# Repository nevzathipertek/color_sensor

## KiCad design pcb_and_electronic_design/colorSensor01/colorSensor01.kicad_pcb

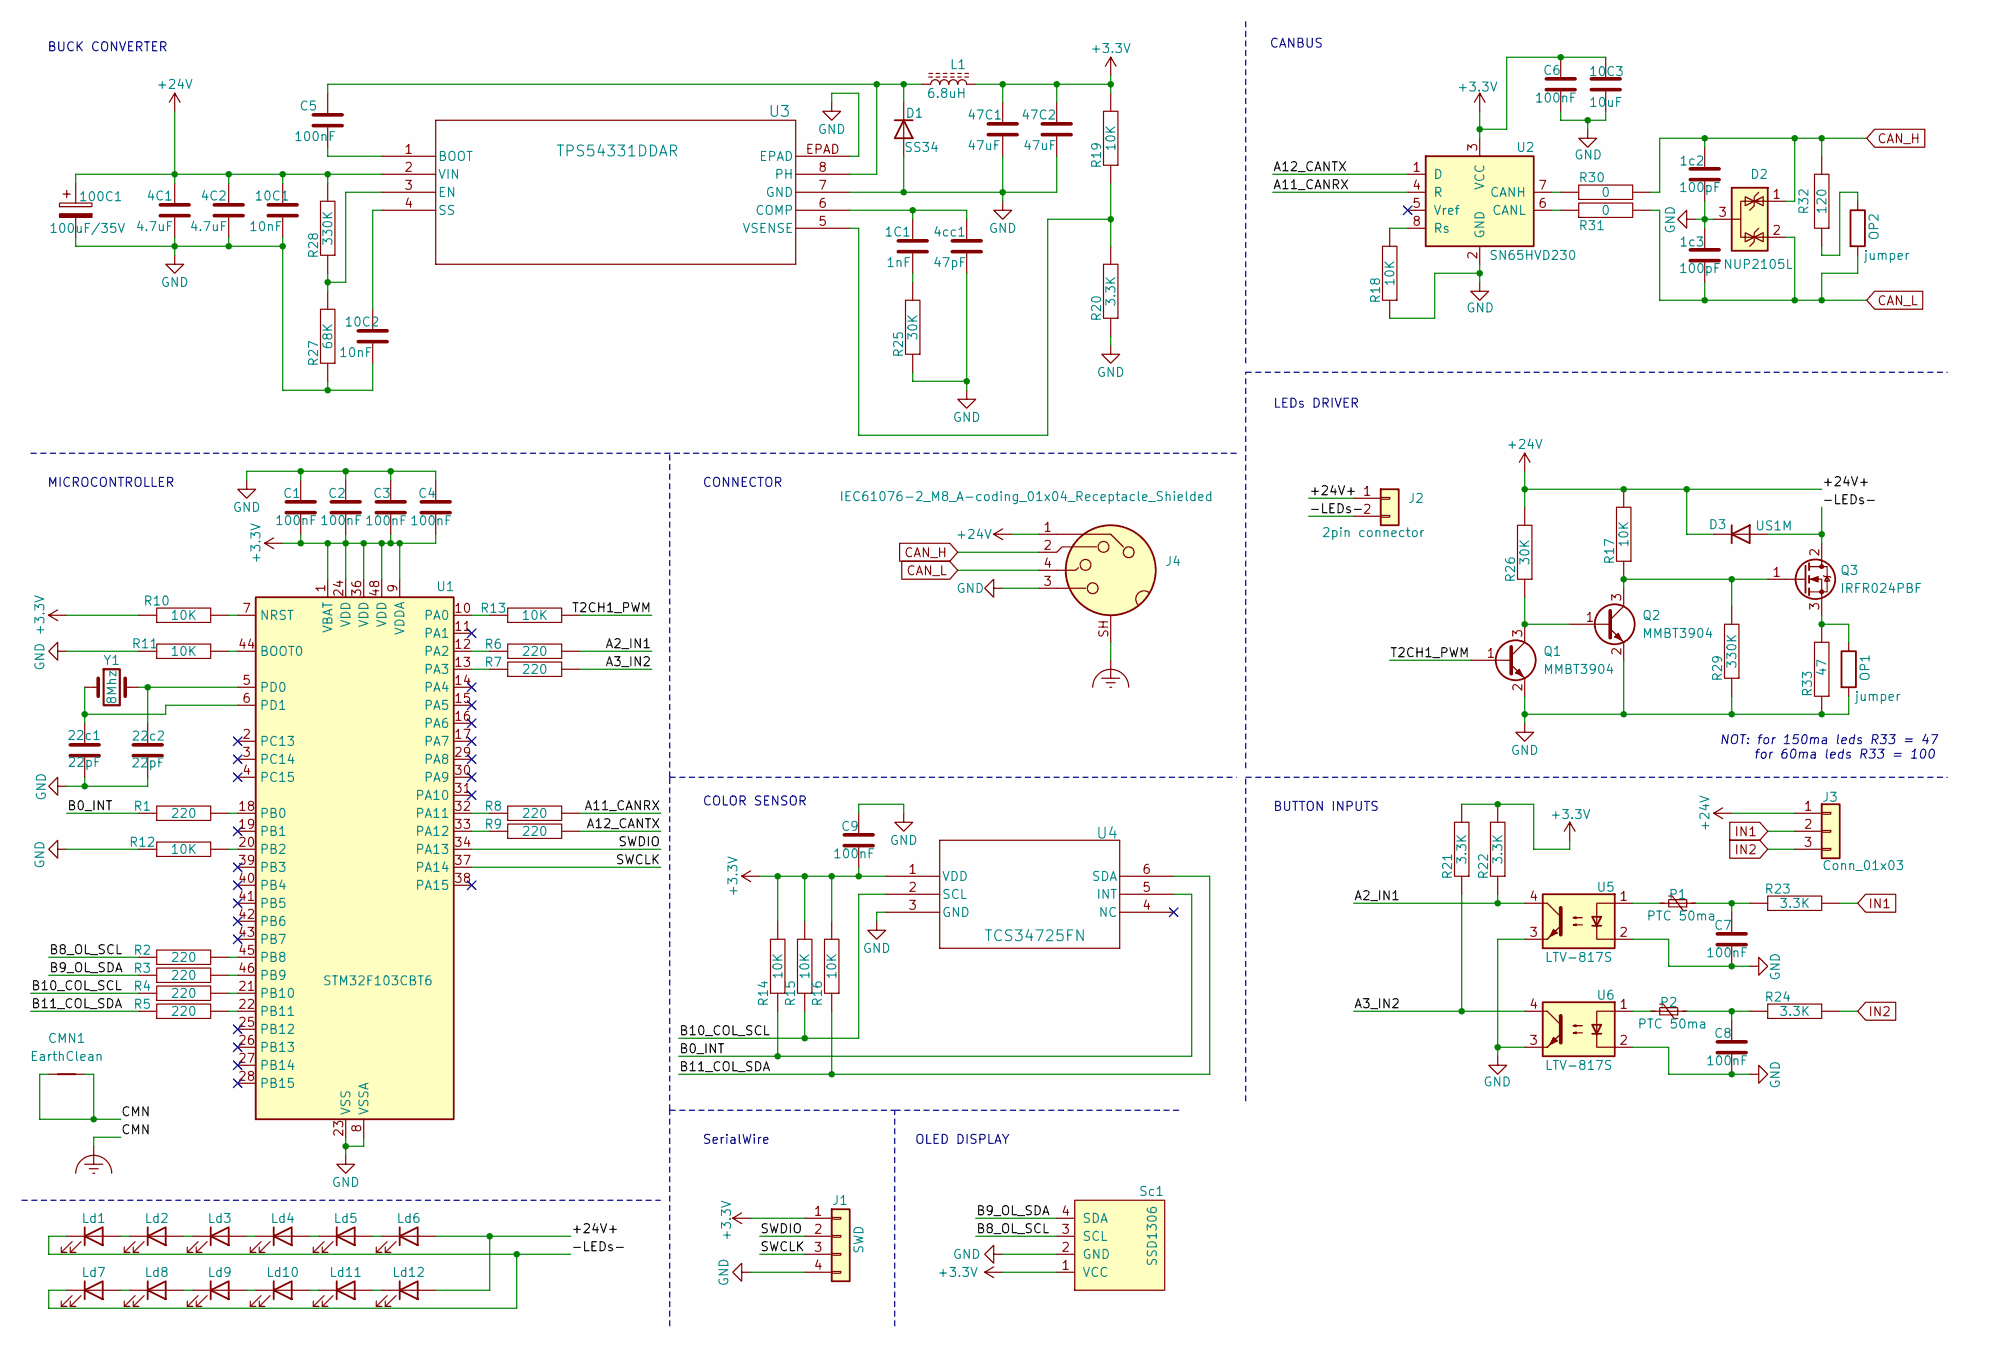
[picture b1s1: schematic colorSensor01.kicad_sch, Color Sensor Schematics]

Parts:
1C1: 1nF; C_0603_1608Metric
1c2, 1c3: 100pF; C_0603_1608Metric
4C1, 4C2: 4.7uF; C_0805_2012Metric
4cc1: 47pF; C_0603_1608Metric
10C1, 10C2: 10nF; C_0603_1608Metric
10C3: 10uF; C_0603_1608Metric
22c1, 22c2: 22pF; C_0603_1608Metric
47C1, 47C2: 47uF; C_0805_2012Metric
100C1: 100uF/35V; CP_Elec_6.3x7.7
C1, C2, C3, C4, C5, C6, C7, C8, C9: 100nF; C_0603_1608Metric
CMN1: EarthClean; NetTie-2_SMD_Pad0.5mm
D1: SS34; D_SMB
D2: NUP2105L; SOT-23
D3: US1M; D_SMA
J1: SWD; PinSocket_1x04_P2.54mm_Vertical
J2: 2pin connector; Molex_KK-254_AE-6410-02A_1x02_P2.54mm_Vertical
J3: Conn_01x03; PinHeader_1x03_P2.54mm_Vertical
J4: IEC61076-2_M8_A-coding_01x04_Receptacle_Shielded; TE_T4041037041-000_M8_04_Socket_Straight
L1: 6.8uH; L_Bourns_SRP7028A_7.3x6.6mm
Ld1, Ld2, Ld3, Ld4, Ld5, Ld6, Ld7, Ld8, Ld9, Ld10, Ld11, Ld12: LED; LED_PLCC_2835
OP1, OP2: jumper; SolderJumper-2_P1.3mm_Open_TrianglePad1.0x1.5mm
P1, P2: PTC 50ma; Fuse_0805_2012Metric
Q1, Q2: MMBT3904; SOT-23
Q3: IRFR024PBF; TO-252-2
R1, R2, R3, R4, R5, R6, R7, R8, R9: 220; R_0603_1608Metric
R10, R11, R12, R13, R14, R15, R16, R17, R18, R19: 10K; R_0603_1608Metric
R20, R21, R22, R23, R24: 3.3K; R_0603_1608Metric
R25, R26: 30K; R_0603_1608Metric
R27: 68K; R_0603_1608Metric
R28, R29: 330K; R_0603_1608Metric
R30, R31: 0; R_0603_1608Metric
R32: 120; R_0603_1608Metric
R33: 47; R_2512_6332Metric
Sc1: SSD1306; 128x64OLED
U1: STM32F103CBT6; LQFP-48_7x7mm_P0.5mm
U2: SN65HVD230; SOIC-8_3.9x4.9mm_P1.27mm
U3: TPS54331DDAR; DDA8_3X2P13-L
U4: TCS34725FN; TCS34725FN_AMS
U5, U6: LTV-817S; SMDIP-4_W9.53mm
Y1: 8Mhz; Crystal_SMD_HC49-SD

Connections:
+3.3V: 10C3.1, 47C1.1, 47C2.1, C1.2, C2.2, C3.2, C4.2, C6.1, C9.2, J1.1, L1.2, R10.1, R14.2, R15.2, R16.2, R19.2, R21.2, R22.2, Sc1.1 (VCC), U1.1 (VBAT), U1.9 (VDDA), U1.24 (VDD), U1.36 (VDD), U1.48 (VDD), U2.3 (VCC), U4.1 (VDD)
+24V: 4C1.1, 4C2.1, 10C1.1, 100C1.1, D3.1 (K), J2.1, J3.1, J4.1, Ld6.2 (A), Ld12.2 (A), R17.2, R26.2, R28.2, U3.2 (VIN)
/-LEDs-: D3.2 (A), J2.2, Ld1.1 (K), Ld7.1 (K), Q3.2 (D)
/A2_IN1: R6.2, R22.1, U5.4
/A3_IN2: R7.2, R21.1, U6.4
/A11_CANRX: R8.2, U2.4 (R)
/A12_CANTX: R9.2, U2.1 (D)
/B0_INT: R1.1, R14.1, U4.5 (INT)
/B8_OL_SCL: R2.1, Sc1.3 (SCL)
/B9_OL_SDA: R3.1, Sc1.4 (SDA)
/B10_COL_SCL: R4.1, R15.1, U4.2 (SCL)
/B11_COL_SDA: R5.1, R16.1, U4.6 (SDA)
/SWCLK: J1.3, U1.37 (PA14)
/SWDIO: J1.2, U1.34 (PA13)
/T2CH1_PWM: Q1.1 (B), R13.2
CAN_H: 1c2.1, D2.1 (K), J4.2, R30.2, R32.2
CAN_L: 1c3.2, D2.2 (K), J4.4, OP2.2, R31.2
Earth_Clean: CMN1.1, CMN1.2, J4.SH
GND: 1c2.2, 1c3.1, 4C1.2, 4C2.2, 4cc1.2, 10C1.2, 10C2.2, 10C3.2, 22c1.2, 22c2.2, 47C1.2, 47C2.2, 100C1.2, C1.1, C2.1, C3.1, C4.1, C6.2, C7.2, C8.2, C9.1, D1.2 (A), D2.3 (A), J1.4, J4.3, OP1.2, Q1.2 (E), Q2.2 (E), R11.1, R12.1, R18.1, R20.1, R25.1, R27.1, R29.1, R33.1, Sc1.2 (GND), U1.8 (VSSA), U1.23 (VSS), U1.35 (VSS), U1.47 (VSS), U2.2 (GND), U3.7 (GND), U3.EPAD, U4.3 (GND), U5.2, U5.3, U6.2, U6.3
IN1: J3.2, R23.2
IN2: J3.3, R24.2
unnamed: 1C1.2, R25.2
unnamed: C7.1, P1.1, R23.1
unnamed: C8.1, P2.1, R24.1
unnamed: C5.1, D1.1 (K), L1.1, U3.8 (PH)
unnamed: Ld1.2 (A), Ld2.1 (K)
unnamed: Ld2.2 (A), Ld3.1 (K)
unnamed: Ld3.2 (A), Ld4.1 (K)
unnamed: Ld4.2 (A), Ld5.1 (K)
unnamed: Ld5.2 (A), Ld6.1 (K)
unnamed: Ld7.2 (A), Ld8.1 (K)
unnamed: Ld8.2 (A), Ld9.1 (K)
unnamed: Ld10.2 (A), Ld11.1 (K)
unnamed: Ld9.2 (A), Ld10.1 (K)
unnamed: Ld11.2 (A), Ld12.1 (K)
unnamed: OP2.1, R32.1
unnamed: P1.2, U5.1
unnamed: P2.2, U6.1
unnamed: Q1.3 (C), Q2.1 (B), R26.1
unnamed: Q2.3 (C), Q3.1 (G), R17.1, R29.2
unnamed: OP1.1, Q3.3 (S), R33.2
unnamed: R11.2, U1.44 (BOOT0)
unnamed: R10.2, U1.7 (NRST)
unnamed: R13.1, U1.10 (PA0)
unnamed: R6.1, U1.12 (PA2)
unnamed: R7.1, U1.13 (PA3)
unnamed: R8.1, U1.32 (PA11)
unnamed: R9.1, U1.33 (PA12)
unnamed: R1.2, U1.18 (PB0)
unnamed: R12.2, U1.20 (PB2)
unnamed: R2.2, U1.45 (PB8)
unnamed: R3.2, U1.46 (PB9)
unnamed: R4.2, U1.21 (PB10)
unnamed: R5.2, U1.22 (PB11)
unnamed: 22c2.1, U1.5 (PD0), Y1.2
unnamed: 22c1.1, U1.6 (PD1), Y1.1
unnamed: R30.1, U2.7 (CANH)
unnamed: R31.1, U2.6 (CANL)
unnamed: R18.2, U2.8 (Rs)
unnamed: C5.2, U3.1 (BOOT)
unnamed: 1C1.1, 4cc1.1, U3.6 (COMP)
unnamed: R27.2, R28.1, U3.3 (EN)
unnamed: 10C2.1, U3.4 (SS)
unnamed: R19.1, R20.2, U3.5 (VSENSE)

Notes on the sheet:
LEDs DRIVER
OLED DISPLAY
BUCK CONVERTER
SerialWire
CONNECTOR
COLOR SENSOR
CANBUS
MICROCONTROLLER
NOT: for 150ma leds R33 = 47 for 60ma leds R33 = 100
BUTTON INPUTS

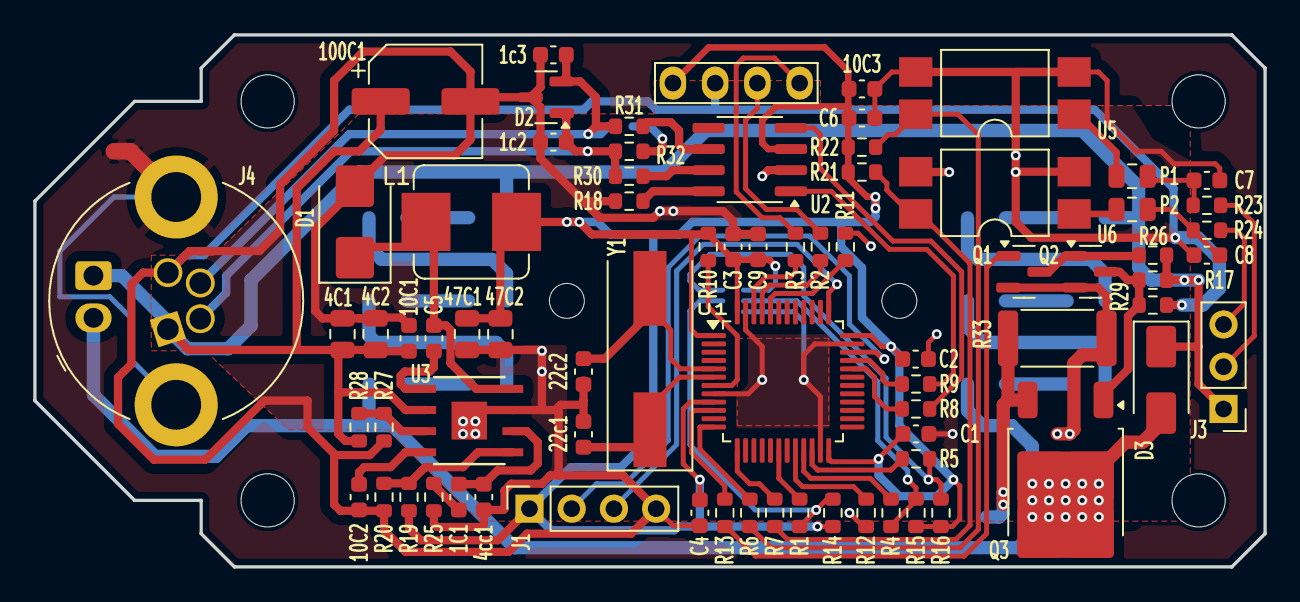
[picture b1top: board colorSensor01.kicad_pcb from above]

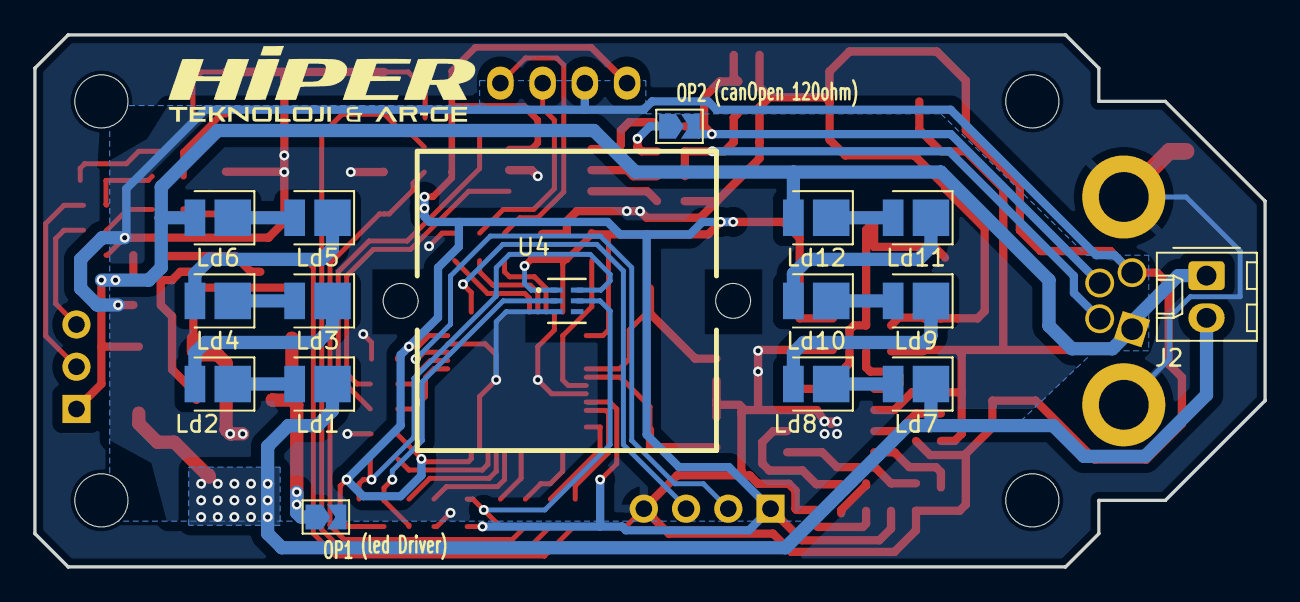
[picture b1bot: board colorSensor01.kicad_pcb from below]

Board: 2 copper layers, 74.0 x 32.0 mm, 99 parts (17 on the bottom side), 64 nets.

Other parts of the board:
H1, H2: MountingHole_2.1mm
H3, H4, H5, H6: MountingHole_3.2mm_M3
HİPER: LOGO

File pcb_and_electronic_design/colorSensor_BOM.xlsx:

Comment | Designator | Footprint | JLCPCB Part #（optional）
PTC 50ma | P2,P1 | Fuse_0805_2012Metric | ptc fuse 50ma
10K | R16,R18,R11,R12,R10,R13,R14,R15,R19,R17 | R_0603_1608Metric
US1M | D3 | D_SMA | Diodes,
3.3K | R24,R20,R23,R21,R22 | R_0603_1608Metric
220 | R4,R3,R1,R6,R8,R5,R9,R2,R7 | R_0603_1608Metric
8Mhz | Y1 | Crystal_SMD_HC49-SD
20pF | 22c1,22c2 | C_0603_1608Metric | 20pF (or 22pF)
100nF | C4,C1,C8,C6,C2,C7,C9,C3,C5 | C_0603_1608Metric
LTV-817S | U6,U5 | SMDIP-4_W9.53mm | LITEON, Optocoupler (or PC817xxx - Diodes Incorporated, SHARP/Socle Technology )
SN65HVD230 | U2 | SOIC-8_3.9x4.9mm_P1.27mm | Texas Instruments,
NUP2105L | D2 | SOT-23 | Onsemi, or Diotec Semiconductor
0 | R31,R30 | R_0603_1608Metric | 0 ohm
TPS54331DDAR | U3 | DDA8_3X2P13-L | Texas Instruments TPS54331DDAR
68K | R27 | R_0603_1608Metric
10nF | 10C1,10C2 | C_0603_1608Metric
MMBT3904 | Q1,Q2 | SOT-23 | Onsemi,
47 | R33 | R_2512_6332Metric
47pF | 4cc1 | C_0603_1608Metric
100pF | 1c2,1c3 | C_0603_1608Metric
6.8uH | L1 | L_Bourns_SRP7028A_7.3x6.6mm | 1A or higher
10uF | 10C3 | C_0603_1608Metric
IRFR024PBF | Q3 | TO-252-2 | Vishay (or Infineon – IRFR540ZTRPBF)
STM32F103CBT6 | U1 | LQFP-48_7x7mm_P0.5mm | must be original ST
47uF | 47C2,47C1 | C_0805_2012Metric
120 | R32 | R_0603_1608Metric
30K | R25,R26 | R_0603_1608Metric
100uF/35V | 100C1 | CP_Elec_6.3x7.7 | 35V ~ 50V
4.7uF | 4C2,4C1 | C_0805_2012Metric
330K | R28,R29 | R_0603_1608Metric
SS34 | D1 | D_SMB
1nF | 1C1 | C_0603_1608Metric
LED | Ld1 – Ld12 | LED_PLCC_2835 | (2835 packet, 2.8V~3.2V, 150~200mA, 60~120degree beam angle) daylight / sunligh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
TCS34725FN | U4 | TCS34725FN_AMS | AMS OSRAM

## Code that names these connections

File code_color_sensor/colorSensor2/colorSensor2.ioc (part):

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Mcu.Name=STM32F103C(8-B)Tx
Mcu.Package=LQFP48
Mcu.UserName=STM32F103CBTx
PA0-WKUP.Signal=S_TIM2_CH1_ETR
PA11.Mode=CAN_Activate
PA11.Signal=CAN_RX
PA12.Mode=CAN_Activate
PA12.Signal=CAN_TX
PA13.Mode=Serial_Wire
PA13.Signal=SYS_JTMS-SWDIO
PA14.Mode=Serial_Wire
PA14.Signal=SYS_JTCK-SWCLK
PA2.GPIOParameters=GPIO_Label
PA2.GPIO_Label=BUTTON1
PA2.Signal=GPIO_Input
PA3.GPIOParameters=GPIO_Label
PA3.GPIO_Label=BUTTON2
PA3.Signal=GPIO_Input
PB0.GPIOParameters=GPIO_Label,GPIO_ModeDefaultEXTI
PB0.GPIO_Label=COLOR_INT_B0
PB0.GPIO_ModeDefaultEXTI=GPIO_MODE_IT_FALLING
PB0.Signal=GPXTI0
PB10.Mode=I2C
PB10.Signal=I2C2_SCL
PB11.Mode=I2C
PB11.Signal=I2C2_SDA
PB2.Signal=GPIO_Output
PB8.GPIOParameters=GPIO_Speed,GPIO_Label
PB8.GPIO_Label=OLED_SCL
PB8.GPIO_Speed=GPIO_SPEED_FREQ_MEDIUM
PB8.Signal=GPIO_Output
PB9.GPIOParameters=GPIO_Speed,GPIO_Label
PB9.GPIO_Label=OLED_SDA
PB9.GPIO_Speed=GPIO_SPEED_FREQ_MEDIUM
PB9.Signal=GPIO_Output
PD0-OSC_IN.Mode=HSE-External-Oscillator
PD0-OSC_IN.Signal=RCC_OSC_IN
PD1-OSC_OUT.Mode=HSE-External-Oscillator
PD1-OSC_OUT.Signal=RCC_OSC_OUT
RCC.SYSCLKFreq_VALUE=72000000
RCC.SYSCLKSource=RCC_SYSCLKSOURCE_PLLCLK
board=custom
